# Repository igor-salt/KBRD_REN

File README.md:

# KBRD_REN
Взято отсюда: https://github.com/ergonautkb/one
Доработано и исправлено

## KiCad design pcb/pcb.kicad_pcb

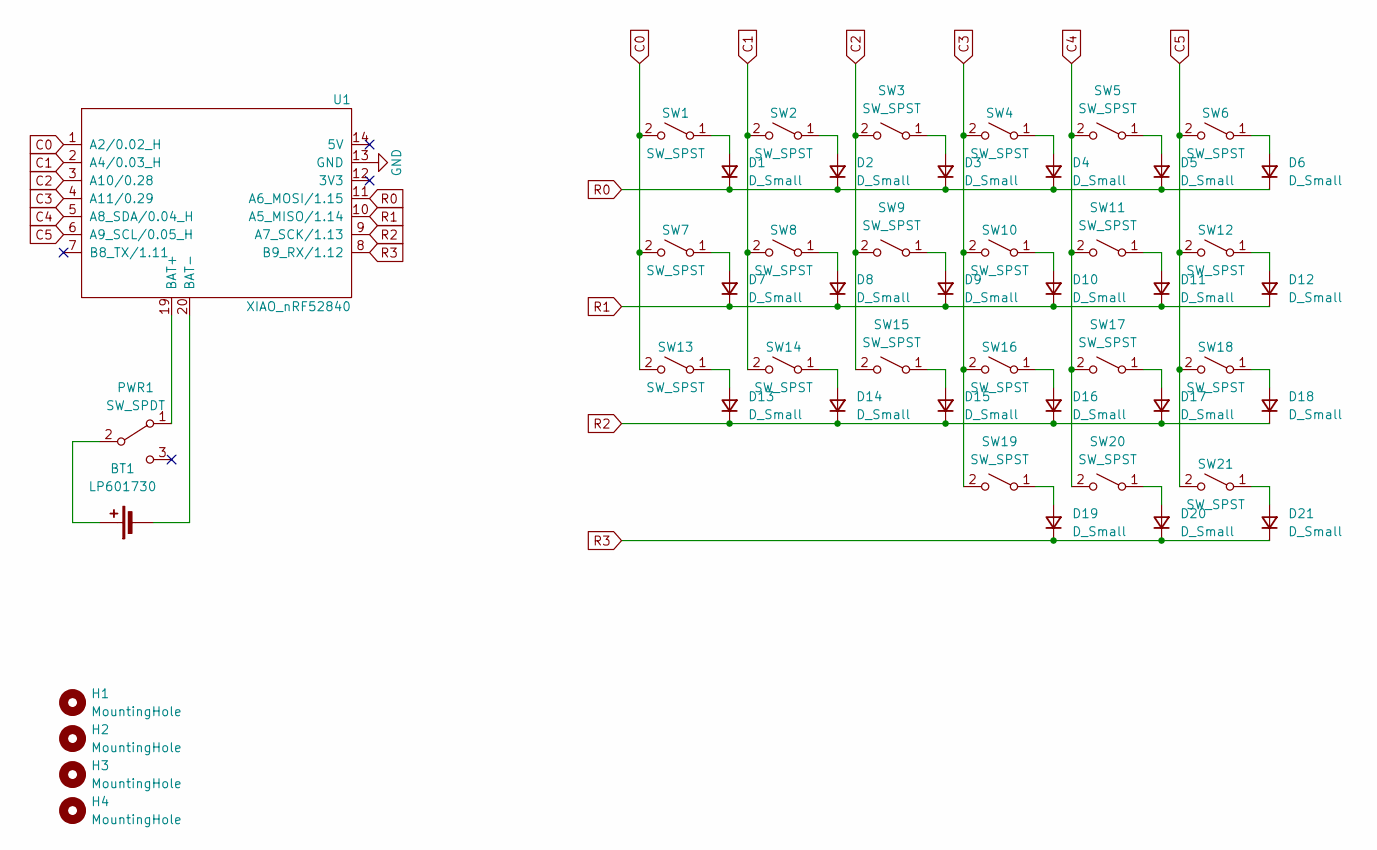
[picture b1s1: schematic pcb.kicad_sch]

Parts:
BT1: LP601730; lp601730
D1, D2, D3, D4, D5, D6, D7, D8, D9, D10, D11, D12, D13, D14, D15, D16, D17, D18, D19, D20, D21: D_Small; Diode_TH_SMD_DUAL
H1, H2, H3, H4: MountingHole; Hole_5.7mm
PWR1: SW_SPDT; MSK-12C02_DUAL
SW1, SW2, SW3, SW4, SW5, SW6, SW7, SW8, SW9, SW10, SW11, SW12, SW13, SW14, SW15, SW16, SW17, SW18, SW19, SW20, SW21: SW_SPST; KS-27_KS-33_Hotswap_1U_DUAL
U1: XIAO_nRF52840; XIAO_nRF52840_DUAL_WINDOW_NO_CAP

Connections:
C0: SW1.2 (B), SW7.2 (B), SW13.2 (B), U1.1 (A2/0.02_H)
C1: SW2.2 (B), SW8.2 (B), SW14.2 (B), U1.2 (A4/0.03_H)
C2: SW3.2 (B), SW9.2 (B), SW15.2 (B), U1.3 (A10/0.28)
C3: SW4.2 (B), SW10.2 (B), SW16.2 (B), SW19.2 (B), U1.4 (A11/0.29)
C4: SW5.2 (B), SW11.2 (B), SW17.2 (B), SW20.2 (B), U1.5 (A8_SDA/0.04_H)
C5: SW6.2 (B), SW12.2 (B), SW18.2 (B), SW21.2 (B), U1.6 (A9_SCL/0.05_H)
GND: U1.13 (GND)
unnamed: BT1.1 (+), PWR1.2 (B)
unnamed: BT1.2 (-), U1.20 (BAT-)
unnamed: D1.2 (A), SW1.1 (A)
unnamed: D2.2 (A), SW2.1 (A)
unnamed: D3.2 (A), SW3.1 (A)
unnamed: D4.2 (A), SW4.1 (A)
unnamed: D5.2 (A), SW5.1 (A)
unnamed: D6.2 (A), SW6.1 (A)
unnamed: D7.2 (A), SW7.1 (A)
unnamed: D8.2 (A), SW8.1 (A)
unnamed: D9.2 (A), SW9.1 (A)
unnamed: D10.2 (A), SW10.1 (A)
unnamed: D11.2 (A), SW11.1 (A)
unnamed: D12.2 (A), SW12.1 (A)
unnamed: D13.2 (A), SW13.1 (A)
unnamed: D14.2 (A), SW14.1 (A)
unnamed: D15.2 (A), SW15.1 (A)
unnamed: D16.2 (A), SW16.1 (A)
unnamed: D17.2 (A), SW17.1 (A)
unnamed: D18.2 (A), SW18.1 (A)
unnamed: D19.2 (A), SW19.1 (A)
unnamed: D20.2 (A), SW20.1 (A)
unnamed: D21.2 (A), SW21.1 (A)
unnamed: PWR1.1 (A), U1.19 (BAT+)
R0: D1.1 (K), D2.1 (K), D3.1 (K), D4.1 (K), D5.1 (K), D6.1 (K), U1.11 (A6_MOSI/1.15)
R1: D7.1 (K), D8.1 (K), D9.1 (K), D10.1 (K), D11.1 (K), D12.1 (K), U1.10 (A5_MISO/1.14)
R2: D13.1 (K), D14.1 (K), D15.1 (K), D16.1 (K), D17.1 (K), D18.1 (K), U1.9 (A7_SCK/1.13)
R3: D19.1 (K), D20.1 (K), D21.1 (K), U1.8 (B9_RX/1.12)

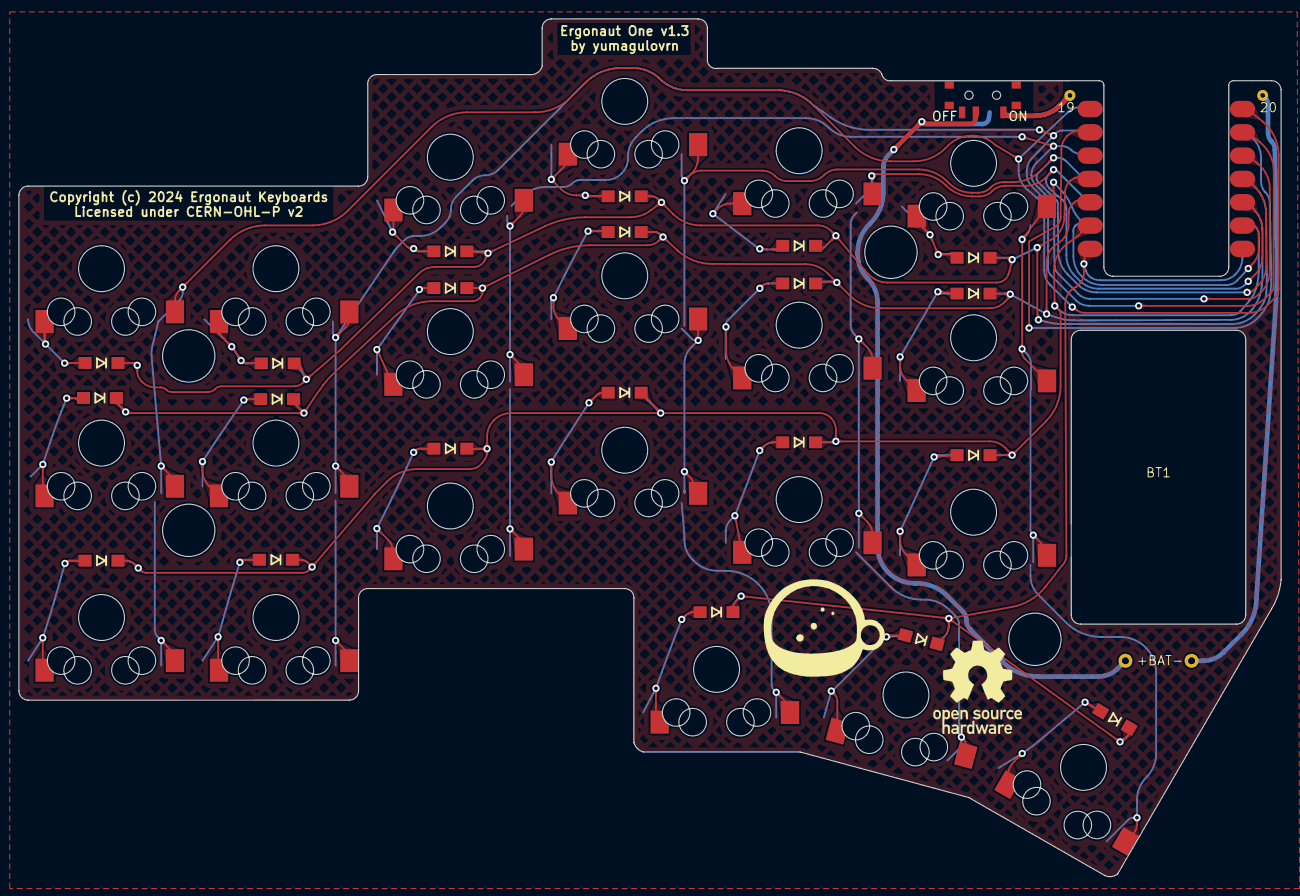
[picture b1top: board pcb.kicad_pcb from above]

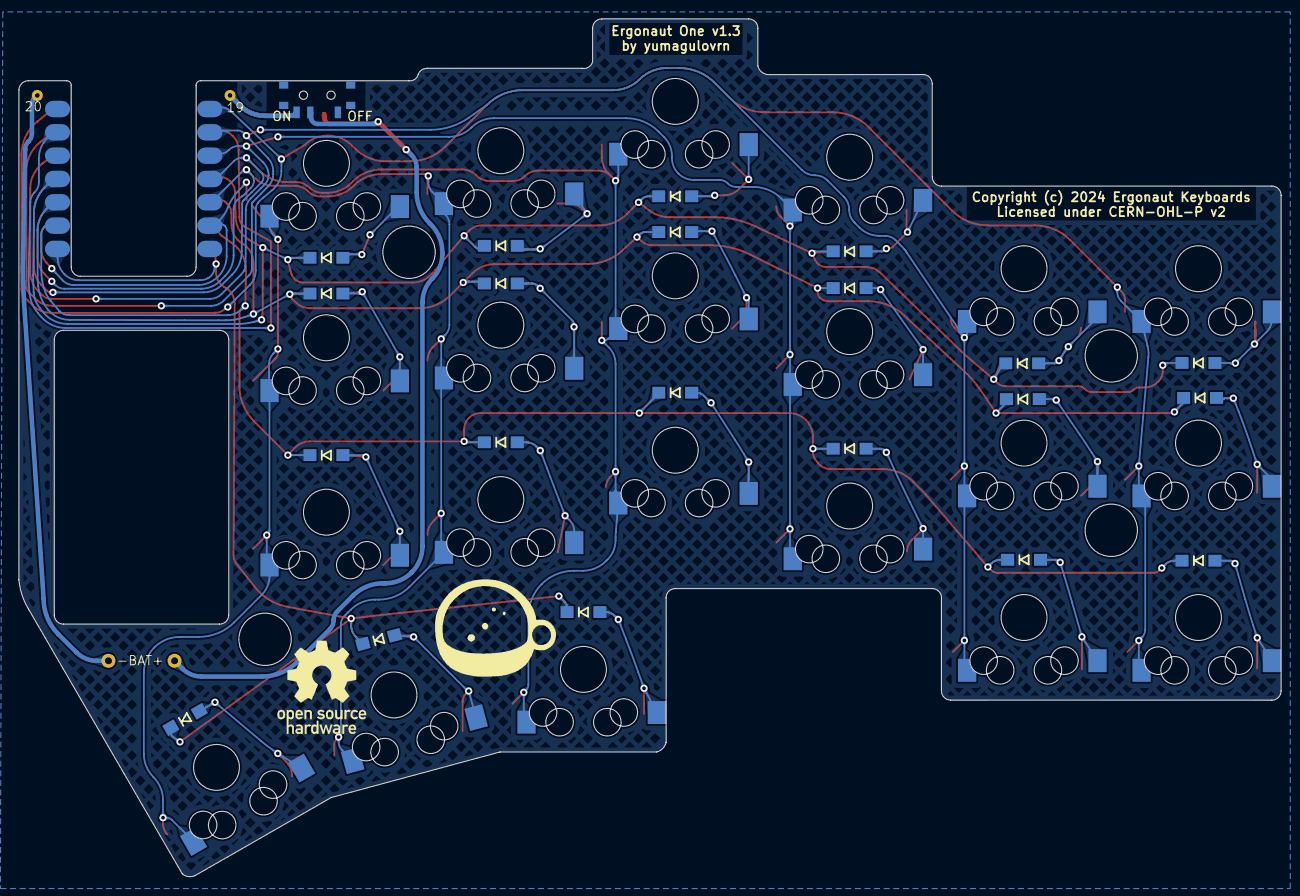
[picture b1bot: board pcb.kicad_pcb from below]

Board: 2 copper layers, 137.5 x 93.4 mm, 49 parts (23 on the bottom side), 34 nets.

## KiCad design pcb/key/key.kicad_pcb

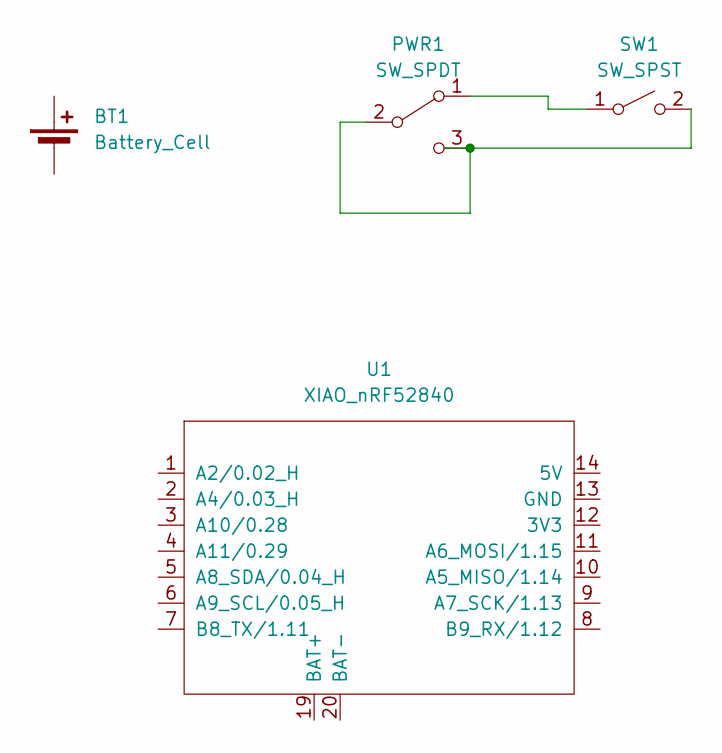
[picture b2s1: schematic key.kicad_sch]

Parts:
BT1: Battery_Cell; lp601730
PWR1: SW_SPDT; MSK-12C02_DUAL
SW1: SW_SPST; KS-27_KS-33_Hotswap_1U_DUAL
U1: XIAO_nRF52840; XIAO_nRF52840_DUAL

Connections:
unnamed: PWR1.1 (A), SW1.1 (A)
unnamed: PWR1.2 (B), PWR1.3 (C), SW1.2 (B)

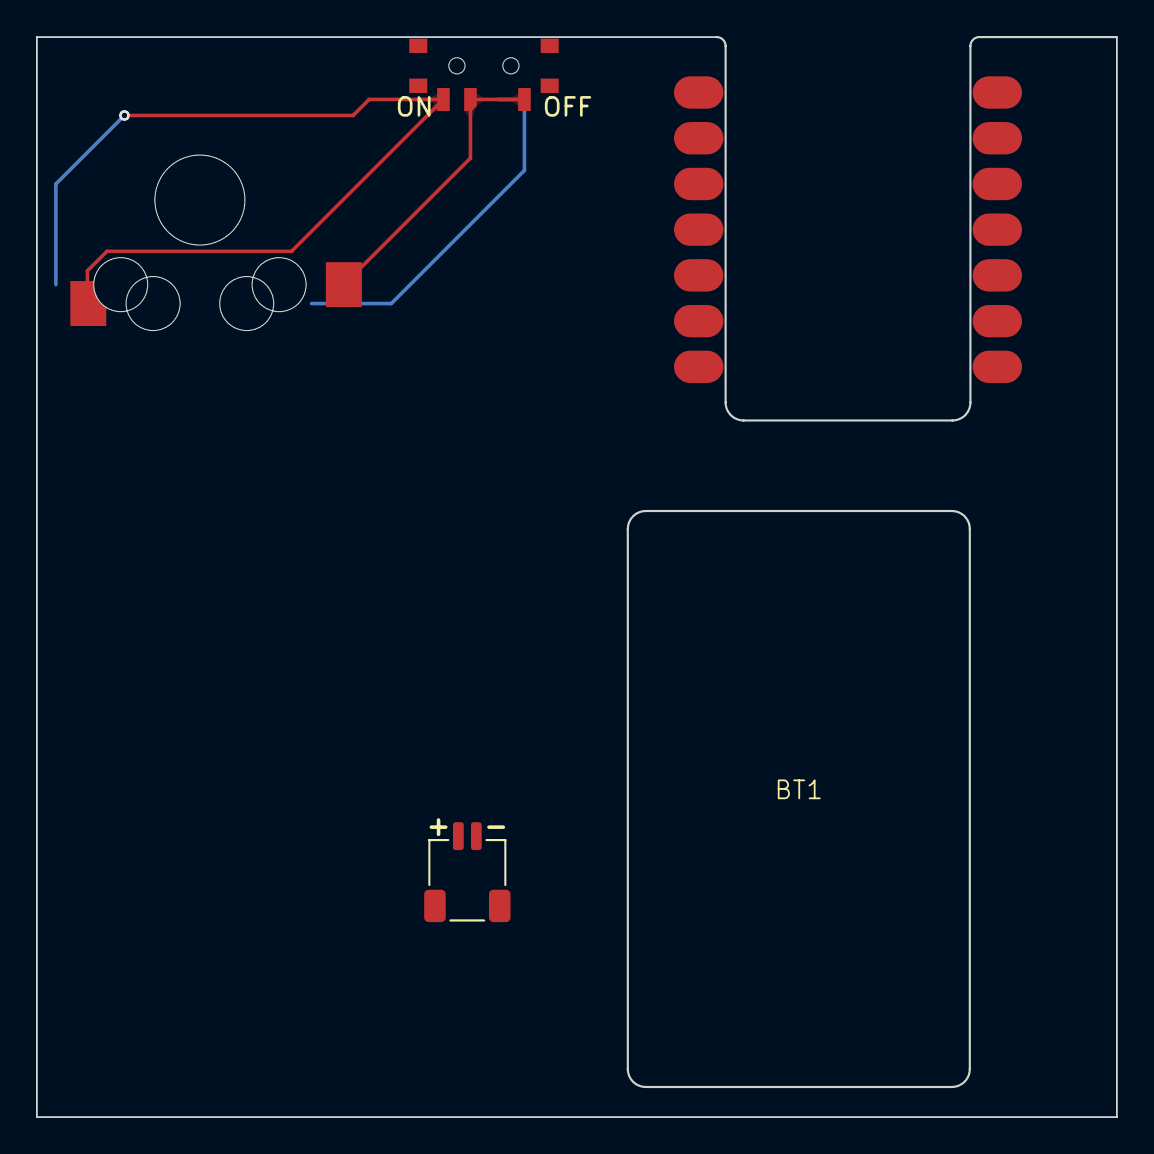
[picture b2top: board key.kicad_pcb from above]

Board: 2 copper layers, 60.0 x 60.0 mm, 5 parts (0 on the bottom side), 2 nets.

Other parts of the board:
J2: Conn_01x02_Pin; JST_SH_Battery_DUAL_

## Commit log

2024-08-27 Начало
    Скопировал исправленную версию
2024-08-27 правка
    несколько дорожек
2024-08-27 диоды двигал
    не окончил
2024-08-28 Готово
    Диоды подвинул
    Клавиши подвинул
    Контур изменил вверху
    Дорожки поправил
    Прежнюю версию заархивировал
2024-08-28 Архив
    Готовую заархивил
2024-08-28 Update LICENSE
2024-08-28 Правка
    Выровнял контур и надпись
2024-08-28 правка
    поправил дорожки и виасы
2024-08-28 Большая правка
    почти хорошо
2024-08-28 Финал
    Вроде всё исправил
2024-08-29 Замена PCB файла на
    присланный Александром с его правками контура. старый переименован
2024-08-29 перерисовал
    включил произвольные углы
2024-08-29 Предварительный финал
    После проверки - в продакшн
2024-08-30 Навёл красоту
    И перевернул проц и разъём питания
2024-08-30 Герберы сгенерировал
    Настройки по умолчанию
    В папке production - файлы для JLCPCB
2024-08-30 Поправил контур
    перезалил медь, перегенерировал герберы
2024-08-30 unlock
2024-08-30 Исправил дорожки
    Которые были близко к краю после правки контура
2024-08-30 ulock
    забыл выйти из редактора
2024-08-31 Исправил легаси - глюк
    Перед тем, как генерировать герберы - надо старые удалять
2024-08-31 выровнял крепёжное отверстие
    и перегенерил герберы
2024-09-04 futprint with windows
2024-09-04 consept
2024-09-13 вырез
2024-09-14 Дорожки развёл
    вокруг окна
2024-09-14 красоту навёл
2024-09-14 Выровнял по Z
2024-09-15 расширил вырез
    и добавил пады питания
2024-09-15 перегенерировал герберы и степ
2024-09-15 добавил батарейку
    и разъём с другой стороны
2024-10-02 in progress
2024-10-03 перевернул
2024-10-07 провода нарисовал
    Размеры поправил
2024-10-07 1.85
2024-10-07 A v1.3
2024-10-08 final
    move 2 ergo

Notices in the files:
pcb/pcb.kicad_pcb:
Copyright (c) 2024 Ergonaut Keyboards
Licensed under CERN-OHL-P v2
